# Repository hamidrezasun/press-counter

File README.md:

# Hydraulic press counter (v6.2)

Counts the strokes of a hydraulic die press, identifies operator and die by NFC card, switches the press contactor through an
on-board relay, shows the counter on a small OLED and reports to an MQTT broker. The stroke signal is the 230 V AC on the press
**contactor coil**, read through an optocoupler.

v6 is the "simple and cheap for mass production" revision: **one board, one chip.** An ESP32-WROOM-32 module does the counting, the relay,
the NFC reader, the display, the temperature probe and WiFi / MQTT / web page. The STM32, the ESP8266, the second board, the ribbon cable,
the 2.4in display and the ribbon cable of v5 are gone. The free ESP32 pins drive four extra output relays (COM / NO / NC) and read two DC inputs
(12/24 V sense, AUX, both 0-30 V). The board runs from 230 V (on-board HLK-5M05) **or** from a 5 V adapter on its own screw terminal (v6.2).
Parts cost about 2.9 M Toman of parts per unit (v5: about 5.1 M), every line checked on a shop page (eca.ir, voltatech.ir, javanelec.com, robochip.ir); without the four output relays about 2.5 M.

```
            ┌──────────────────────────── one board, 202 x 104 mm ────────────────────────────┐
 230 V ────►│ fuse · HLK-5M05 5 V (or 5 V adapter) · LDO ESP32-WROOM-32 (WiFi)    OLED 0.96in  │
 contactor ►│ 230 VAC opto input (MB10S + PC817)       USB micro-B (CH340G)      RC522 NFC    │
 coil       │ relay 5 V (COM / NO / NC) ──► press contactor control circuit                    │
            │ DS18B20 probe terminal · 2 call buttons · buzzer · LEDs                           │
            │ 4 output relays (COM / NO / NC) · 12/24 V and AUX inputs (0-30 V)                   │
            └───────────────────────────────────────────────────────────────────────────────────┘
```

| Folder | What |
|--------|------|
| `hardware/` | KiCad 10 project (generated from `tools/design.py`), fabrication files, BOM with Iranian-store links - [hardware/README.md](hardware/README.md) |
| `firmware/press_counter/` | the ESP32 firmware (Arduino sketch) - [docs/FIRMWARE.md](docs/FIRMWARE.md) |
| `docs/` | [DESIGN_REVIEW.md](docs/DESIGN_REVIEW.md) block-by-block check with calculations and open points, [PRODUCTION.md](docs/PRODUCTION.md) what to send to the board house / assembler and how to test, [INSTALLATION.md](docs/INSTALLATION.md) enclosure, wiring, labels, safety limits, [LASER_DIY.md](docs/LASER_DIY.md) prototype with a laser + drill, [ORDER_ESYS.md](docs/ORDER_ESYS.md) ordering at esys.ir, [SOURCING.md](docs/SOURCING.md) which shops (eca.ir + voltatech.ir cover everything), [FIRMWARE.md](docs/FIRMWARE.md), [PROTOCOL.md](docs/PROTOCOL.md) (MQTT topics, HTTP API), [REVIEW.md](docs/REVIEW.md) history of the design decisions |
| `hardware/archive_v5/`, `firmware/archive_v5/` | the previous two-board STM32 + ESP8266 design (reference only) |
| `V2/` | the old single-ESP8266 firmware for the v2 board (kept) |
| `analyzer/` | FastAPI + React dashboard that turns InfluxDB events into work sessions (needs an MQTT -> InfluxDB bridge such as Telegraf) |

## What it does

* **Strokes:** one MQTT event per stroke: `count`, `duration` (ms the contactor was energised), `temperature`; the lifetime counter survives power loss.
* **Who / what:** `personnel:<id>` card = start / end of a work session, switches the relay (enables the press); `die:<id>` card = which die is mounted.
* **Machine relay:** COM / NO / NC on a terminal; with COM-NO in the contactor control circuit the press is *disabled* whenever the board is unpowered, reset or hung (watchdog). Idle timeout and over-temperature switch it off. Remote start over the network is refused unless it was enabled in the settings; stop always works.
* **Local:** OLED with the counter, machine state, operator, temperature, errors (`Exx`), calls and the IP address; two call buttons (supervisor, net / maintenance), buzzer, red alarm LED, green "machine on" LED. Works without any network.
* **Extra I/O:** four output relays OUT1-OUT4 (COM / NO / NC, MQTT `relay/2..5/set`, or automatic: follow the machine, an alarm, a call, the press signal); 12/24 V sense input and AUX input, both 0-30 V (MQTT `sensor/voltage`).
* **Network:** WiFi with a setup access point, NTP, **MQTT** (status, events, `relay/1/set`, `cmd`), web page with every function and setting, ArduinoOTA and updates from your own server.
* **Power:** 230 VAC on J1, or a regulated 5 V adapter on J6 (protected: resettable fuse, TVS, reverse-polarity diode). No relay clicks while the board starts, resets or is programmed.
* **Programming:** one micro-USB cable, Arduino IDE (*ESP32 Dev Module*): the board's CH340G resets the ESP32 into its bootloader by itself, like an Arduino.

## Where it stands (honest status)

| Part | State |
|------|-------|
| PCB | 202 x 104 mm, 124 parts. ERC 0, DRC 0 violations / 0 unconnected / schematic parity OK (KiCad 10); the 5 mm mains creepage rule was shown to trigger on a deliberately wrong placement. **Never fabricated or powered.** Several footprints of generic parts must be checked against the real parts first - [docs/DESIGN_REVIEW.md](docs/DESIGN_REVIEW.md) section 8 |
| Firmware | **compiles** for the ESP32 (Arduino core esp32 3.3.12, no warnings with all warnings on): 1,248,699 bytes of the 1.9 MB app partition, 68.6 KB static RAM. **Never run on a chip** |
| Web page | checked in a browser against a mock (`firmware/tools/mock_device.py`) |
| Mains parts | 5 mm creepage enforced between mains and low voltage, 1 A time-lag fuse on the board; the relay coil / contact insulation is *basic* only - **a qualified person must do the mains wiring and first power-up** |

## Quick start

1. Read [docs/PRODUCTION.md](docs/PRODUCTION.md). Build 3-5 pilot boards first; order the PCB from `hardware/fabrication/main/press_counter_gerbers.zip` and the parts from `hardware/BOM_press_counter_v6.xlsx` (check the footprints of the real parts, see DESIGN_REVIEW).
2. Flash the firmware over USB from the Arduino IDE - [docs/FIRMWARE.md](docs/FIRMWARE.md).
3. Join the setup WiFi `PressCounter-XXXXXX` (password `presscounter`), enter your WiFi, then open the device's page (its IP is on the display): set the MQTT broker, an **admin password** and the OTA password.
4. Wire the contactor coil to `PRESS SENSE 230VAC` (J2), the press-contactor control circuit to the relay contact (J5, COM / NO), the DS18B20 probe to J4, mains to J1 (the 1 A fuse F1 is on the board). Never run the board with the enclosure open.

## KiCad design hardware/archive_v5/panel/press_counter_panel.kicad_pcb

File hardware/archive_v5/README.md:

# Archive: press counter v5 (two boards, STM32F103 + ESP8266)

Kept for reference only - superseded by the single-board ESP32 design v6 (see ../README.md).

* `fabrication/` - the last complete, DRC-clean v5.2 exports (MAIN 188 x 104 mm with five relays, PANEL 150 x 96 mm).
* `main/`, `panel/` - KiCad projects as they were when v6 was started (MAIN contains the unfinished v5.3 USB-programming changes).
* `tools/` - the v5 generator scripts (design.py, layout_main.py, layout_panel.py ...); they expect to live in `hardware/tools/`.
* `BOM_press_counter_v5.xlsx` - BOM of v5.3 (about 5.1 M Toman).

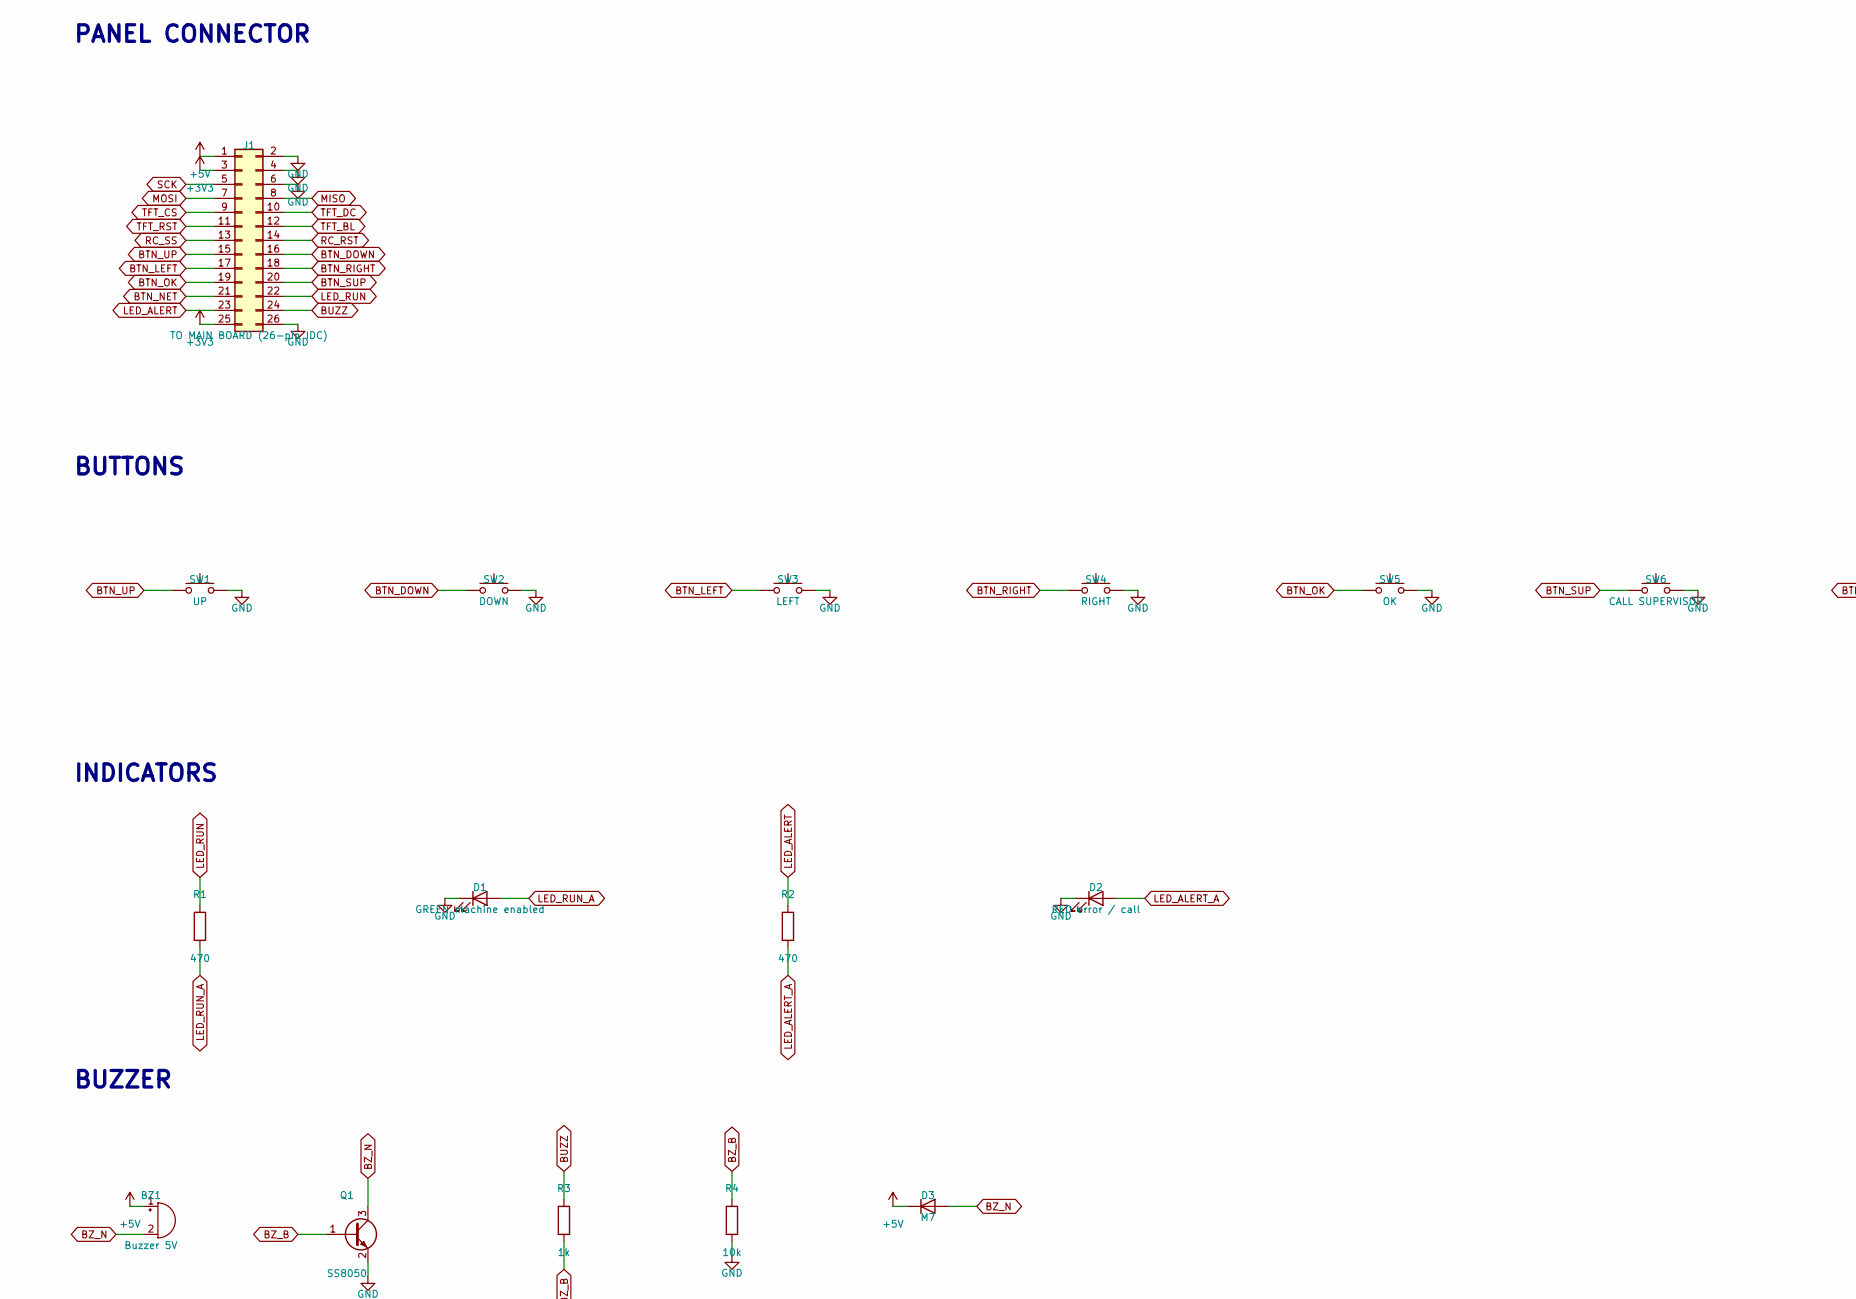
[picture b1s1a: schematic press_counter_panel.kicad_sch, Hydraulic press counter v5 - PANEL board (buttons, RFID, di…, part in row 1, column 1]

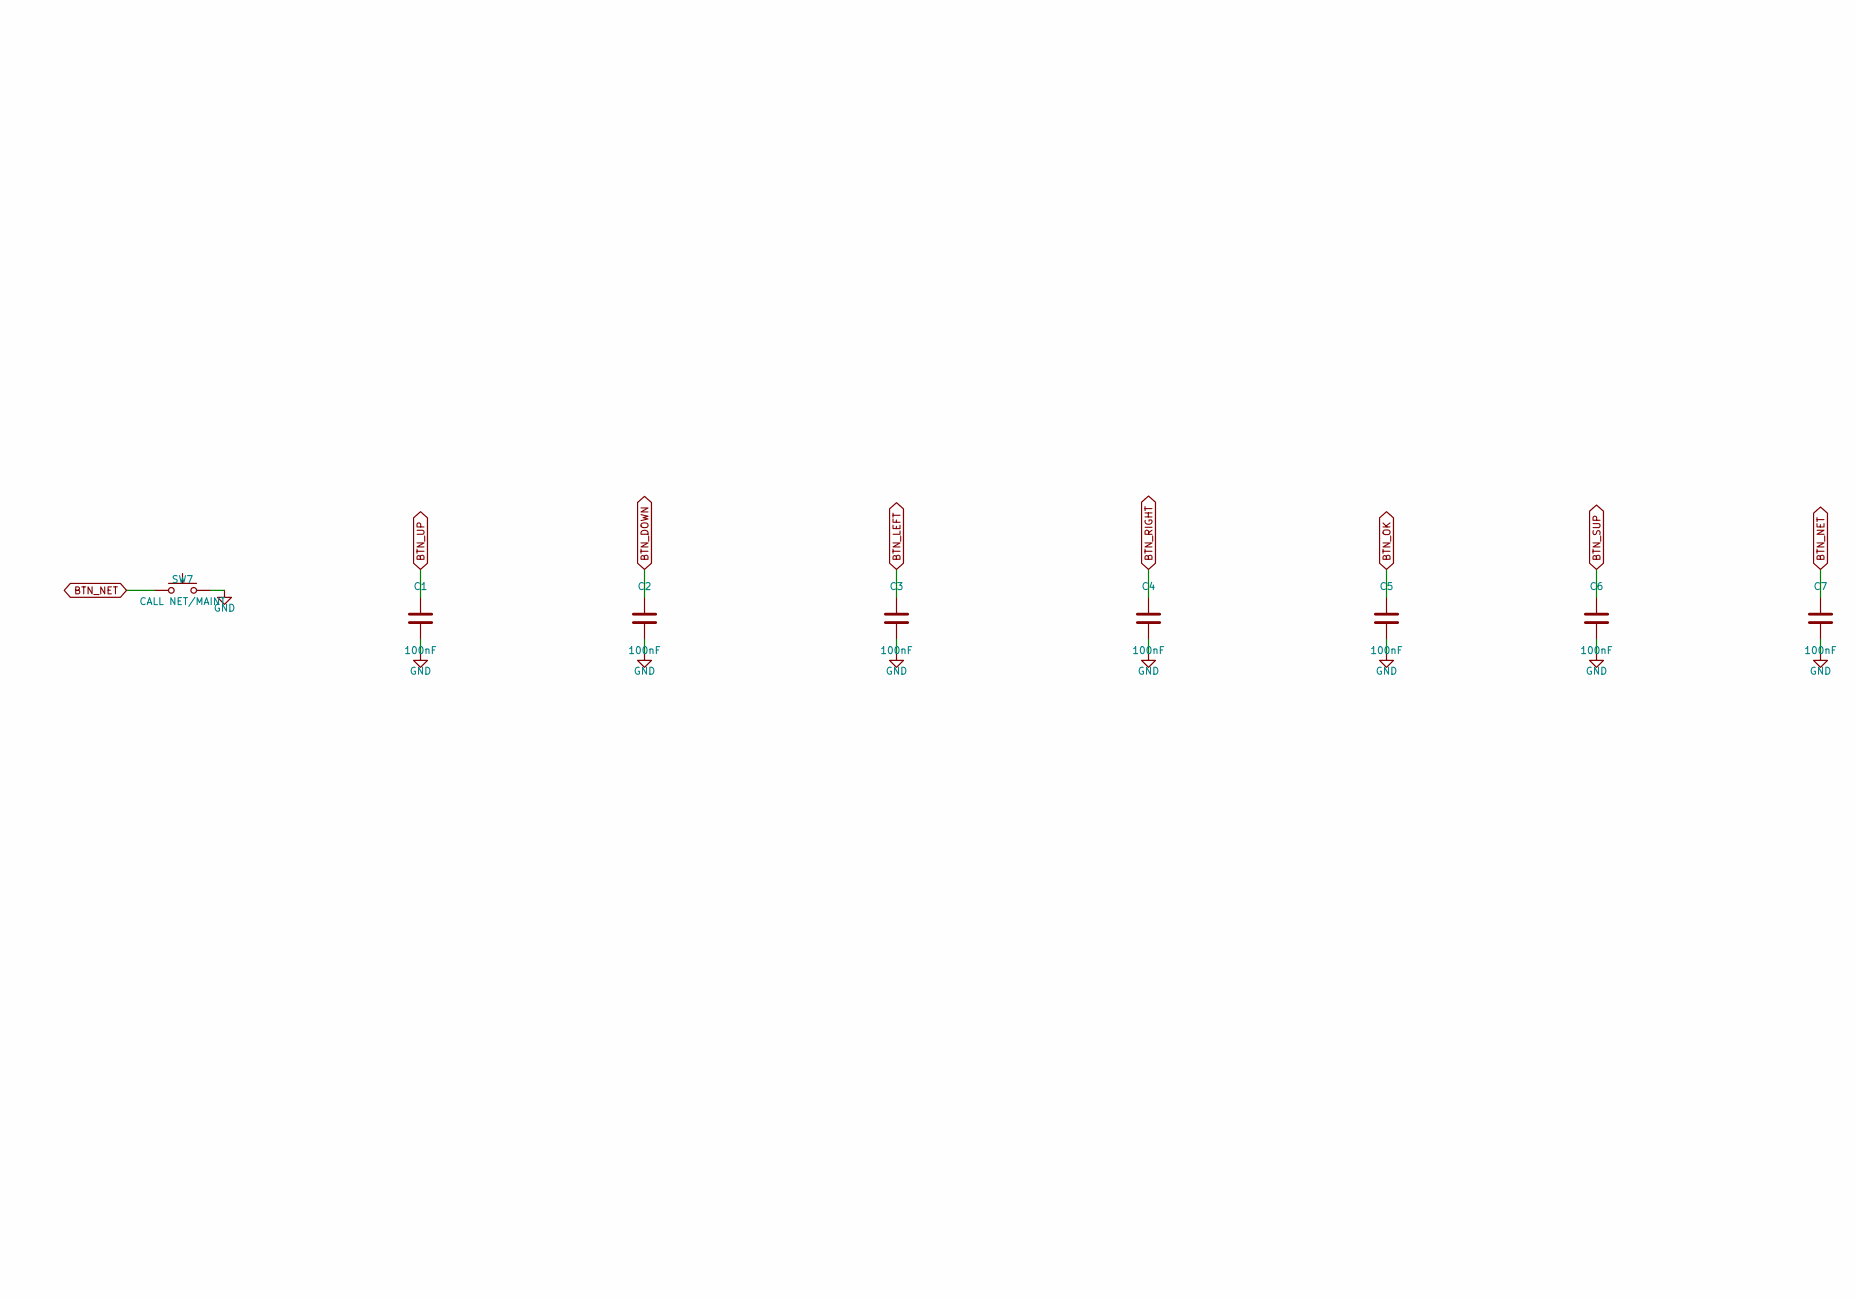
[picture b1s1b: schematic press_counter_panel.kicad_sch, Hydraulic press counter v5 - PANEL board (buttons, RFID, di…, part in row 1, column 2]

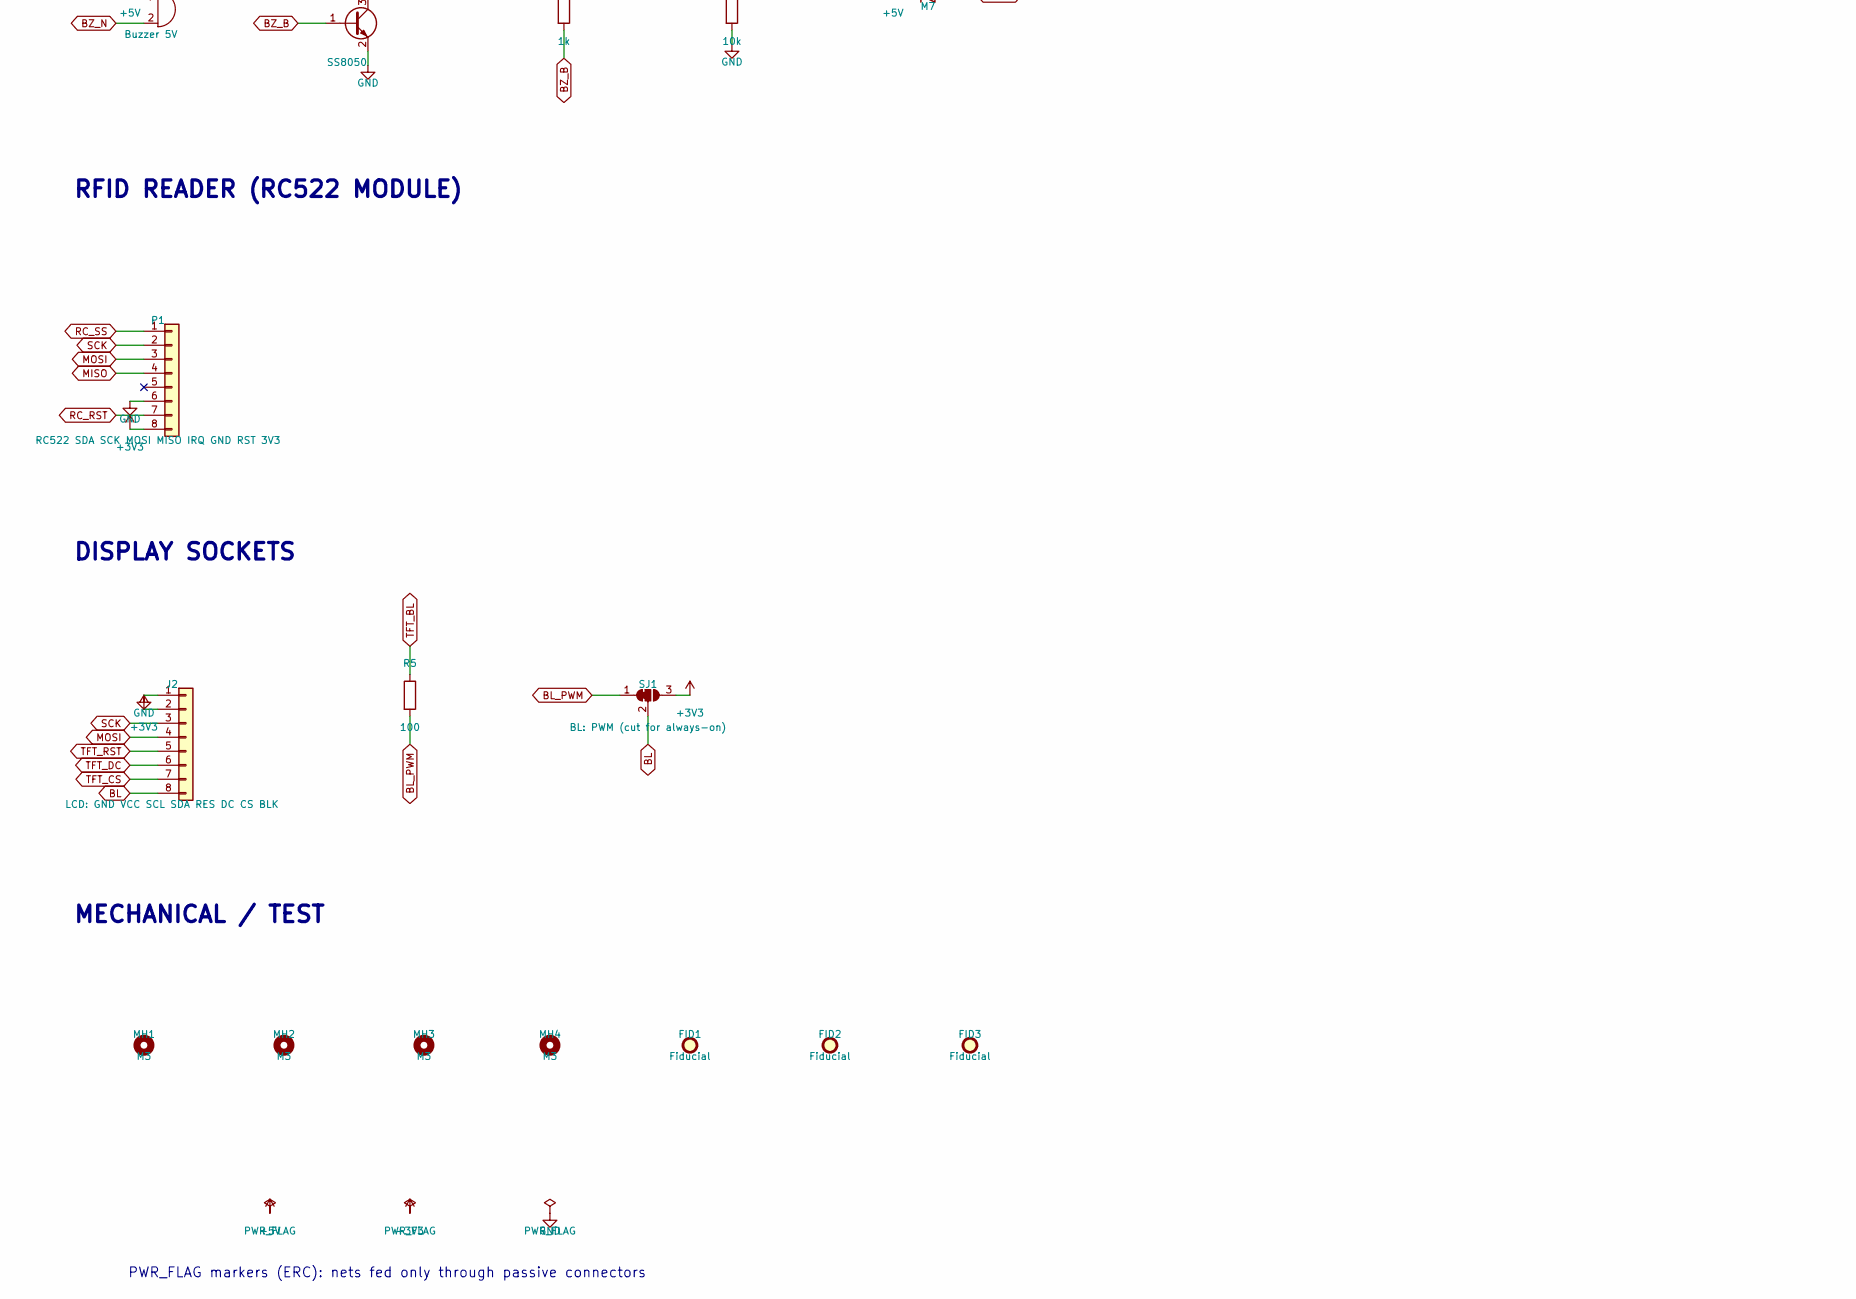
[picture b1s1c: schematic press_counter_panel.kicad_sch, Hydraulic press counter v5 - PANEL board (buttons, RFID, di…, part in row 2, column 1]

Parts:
BZ1: Buzzer 5V; Buzzer_12x9.5RM7.6
C1, C2, C3, C4, C5, C6, C7: 100nF; C_1206_3216Metric
D1: GREEN machine enabled; LED_0805_2012Metric
D2: RED error / call; LED_0805_2012Metric
D3: M7; D_SMA
FID1, FID2, FID3: Fiducial; Fiducial_1mm_Mask2mm
J1: TO MAIN BOARD (26-pin IDC); IDC-Header_2x13_P2.54mm_Vertical
J2: LCD: GND VCC SCL SDA RES DC CS BLK; PinSocket_1x08_P2.54mm_Vertical
MH1, MH2, MH3, MH4: M3; MountingHole_3.2mm_M3
P1: RC522 SDA SCK MOSI MISO IRQ GND RST 3V3; PinSocket_1x08_P2.54mm_Vertical
Q1: SS8050; SOT-23
R1, R2: 470; R_0805_2012Metric
R3: 1k; R_0805_2012Metric
R4: 10k; R_0805_2012Metric
R5: 100; R_0805_2012Metric
SJ1: BL: PWM (cut for always-on); SolderJumper-3_P1.3mm_Bridged12_Pad1.0x1.5mm
SW1: UP; SW_SPST_B3S-1000
SW2: DOWN; SW_SPST_B3S-1000
SW3: LEFT; SW_SPST_B3S-1000
SW4: RIGHT; SW_SPST_B3S-1000
SW5: OK; SW_SPST_B3S-1000
SW6: CALL SUPERVISOR; SW_SPST_B3S-1000
SW7: CALL NET/MAINT; SW_SPST_B3S-1000

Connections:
+3V3: J1.3, J1.25, J2.2, P1.8, SJ1.3 (B)
+5V: BZ1.1 (+), D3.1 (K), J1.1
BL: J2.8, SJ1.2 (C)
BL_PWM: R5.2, SJ1.1 (A)
BTN_DOWN: C2.1, J1.16, SW2.1
BTN_LEFT: C3.1, J1.17, SW3.1
BTN_NET: C7.1, J1.21, SW7.1
BTN_OK: C5.1, J1.19, SW5.1
BTN_RIGHT: C4.1, J1.18, SW4.1
BTN_SUP: C6.1, J1.20, SW6.1
BTN_UP: C1.1, J1.15, SW1.1
BUZZ: J1.24, R3.1
BZ_B: Q1.1 (B), R3.2, R4.1
BZ_N: BZ1.2 (-), D3.2 (A), Q1.3 (C)
GND: C1.2, C2.2, C3.2, C4.2, C5.2, C6.2, C7.2, D1.1 (K), D2.1 (K), J1.2, J1.4, J1.6, J1.26, J2.1, P1.6, Q1.2 (E), R4.2, SW1.2, SW2.2, SW3.2, SW4.2, SW5.2, SW6.2, SW7.2
LED_ALERT: J1.23, R2.1
LED_ALERT_A: D2.2 (A), R2.2
LED_RUN: J1.22, R1.1
LED_RUN_A: D1.2 (A), R1.2
MISO: J1.8, P1.4
MOSI: J1.7, J2.4, P1.3
RC_RST: J1.14, P1.7
RC_SS: J1.13, P1.1
SCK: J1.5, J2.3, P1.2
TFT_BL: J1.12, R5.1
TFT_CS: J1.9, J2.7
TFT_DC: J1.10, J2.6
TFT_RST: J1.11, J2.5

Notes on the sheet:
PANEL CONNECTOR
BUTTONS
INDICATORS
BUZZER
RFID READER (RC522 MODULE)
DISPLAY SOCKETS
MECHANICAL / TEST
PWR_FLAG markers (ERC): nets fed only through passive connectors

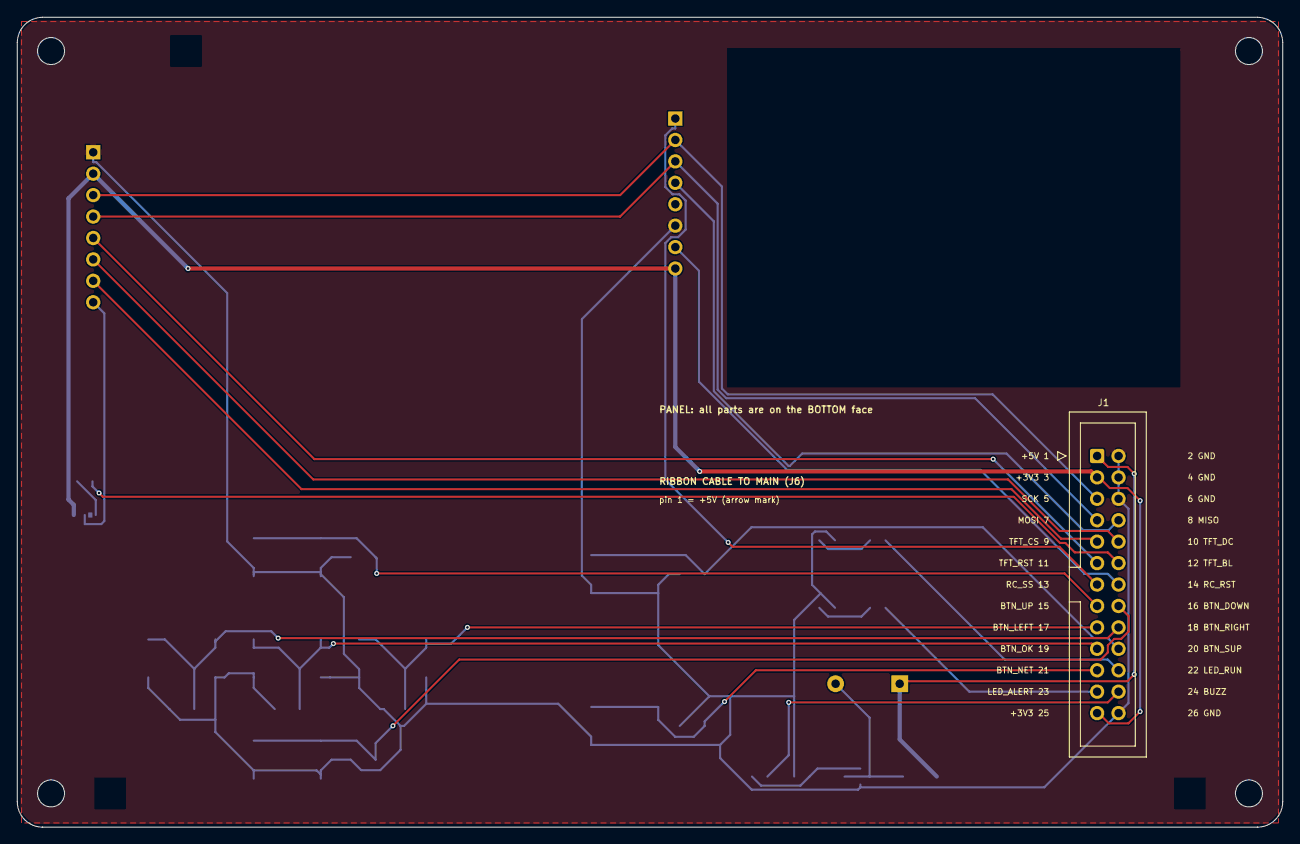
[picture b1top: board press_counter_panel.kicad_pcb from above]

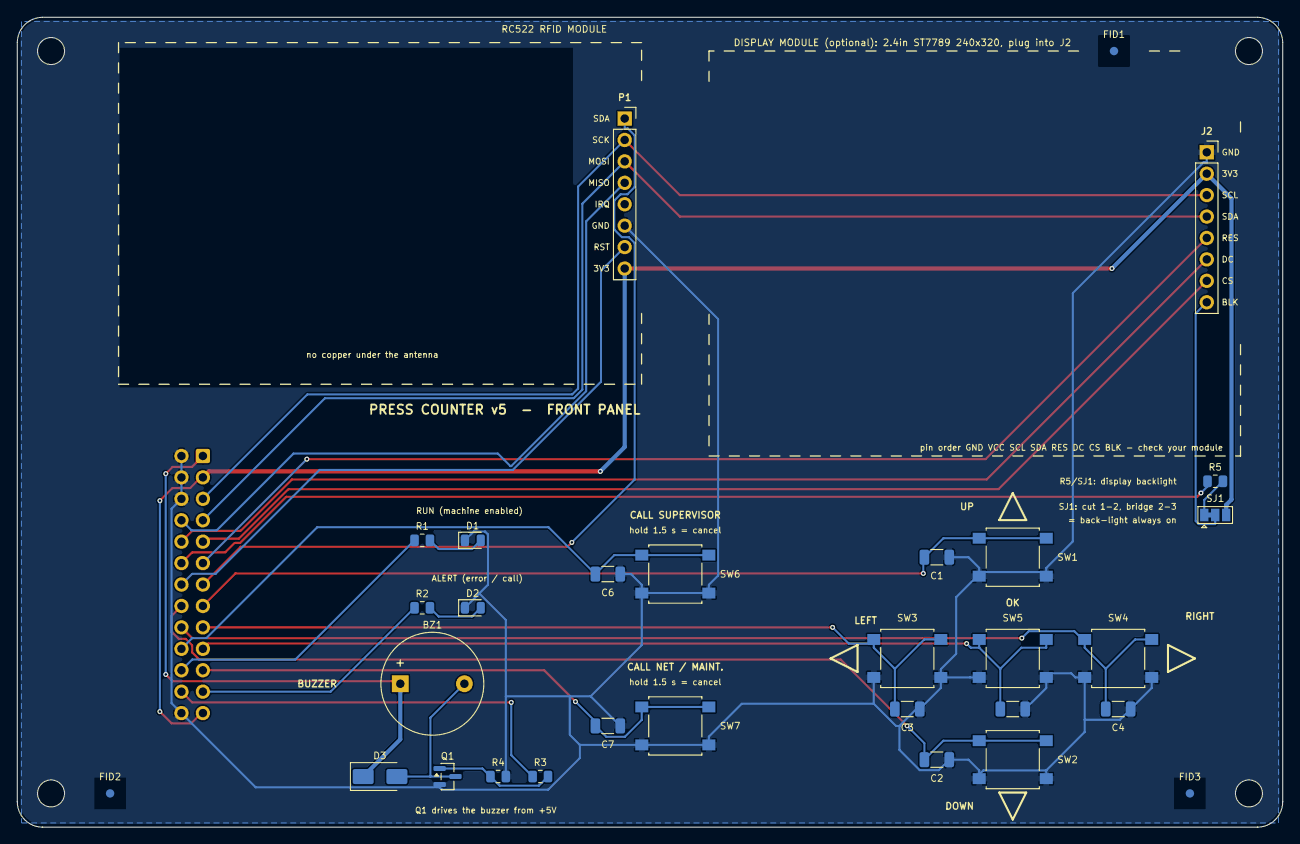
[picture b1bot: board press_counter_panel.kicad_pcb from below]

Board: 2 copper layers, 150.0 x 96.0 mm, 35 parts (30 on the bottom side), 28 nets.

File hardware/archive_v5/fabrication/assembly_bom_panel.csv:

Designator,Value,Footprint,Description,Mounting + side,DNP,Group
J1,TO MAIN BOARD (26-pin IDC),IDC-Header_2x13_P2.54mm_Vertical,IDC box header 2x13 + 26-wire ribbon cable,THT top,,PANEL CONNECTOR
SW1,UP,SW_SPST_B3S-1000,Tactile switch 6x6x5 SMD,SMD bottom,,BUTTONS
SW2,DOWN,SW_SPST_B3S-1000,Tactile switch 6x6x5 SMD,SMD bottom,,BUTTONS
SW3,LEFT,SW_SPST_B3S-1000,Tactile switch 6x6x5 SMD,SMD bottom,,BUTTONS
SW4,RIGHT,SW_SPST_B3S-1000,Tactile switch 6x6x5 SMD,SMD bottom,,BUTTONS
SW5,OK,SW_SPST_B3S-1000,Tactile switch 6x6x5 SMD,SMD bottom,,BUTTONS
SW6,CALL SUPERVISOR,SW_SPST_B3S-1000,Tactile switch 6x6x5 SMD,SMD bottom,,BUTTONS
SW7,CALL NET/MAINT,SW_SPST_B3S-1000,Tactile switch 6x6x5 SMD,SMD bottom,,BUTTONS
C1,100nF,C_1206_3216Metric,100nF 50V X7R 1206,SMD bottom,,BUTTONS
C2,100nF,C_1206_3216Metric,100nF 50V X7R 1206,SMD bottom,,BUTTONS
C3,100nF,C_1206_3216Metric,100nF 50V X7R 1206,SMD bottom,,BUTTONS
C4,100nF,C_1206_3216Metric,100nF 50V X7R 1206,SMD bottom,,BUTTONS
C5,100nF,C_1206_3216Metric,100nF 50V X7R 1206,SMD bottom,,BUTTONS
C6,100nF,C_1206_3216Metric,100nF 50V X7R 1206,SMD bottom,,BUTTONS
C7,100nF,C_1206_3216Metric,100nF 50V X7R 1206,SMD bottom,,BUTTONS
R1,470,R_0805_2012Metric,470R 0805,SMD bottom,,INDICATORS
D1,GREEN machine enabled,LED_0805_2012Metric,LED 0805 green,SMD bottom,,INDICATORS
R2,470,R_0805_2012Metric,470R 0805,SMD bottom,,INDICATORS
D2,RED error / call,LED_0805_2012Metric,LED 0805 red,SMD bottom,,INDICATORS
BZ1,Buzzer 5V,Buzzer_12x9.5RM7.6,Buzzer 12mm 5V (active),THT bottom,,BUZZER
Q1,SS8050,SOT-23,SS8050 SOT-23,SMD bottom,,BUZZER
R3,1k,R_0805_2012Metric,1k 0805,SMD bottom,,BUZZER
R4,10k,R_0805_2012Metric,10k 0805,SMD bottom,,BUZZER
D3,M7,D_SMA,1N4007 SMD (M7),SMD bottom,,BUZZER
P1,RC522 SDA SCK MOSI MISO IRQ GND RST 3V3,PinSocket_1x08_P2.54mm_Vertical,Female header 1x8 (for the RC522 module),THT bottom,,RFID READER (RC522 MODULE)
J2,LCD: GND VCC SCL SDA RES DC CS BLK,PinSocket_1x08_P2.54mm_Vertical,Female header 1x8 (2.4in ST7789 display module),THT bottom,optional (display),DISPLAY SOCKETS
R5,100,R_0805_2012Metric,100R 0805,SMD bottom,optional (display),DISPLAY SOCKETS

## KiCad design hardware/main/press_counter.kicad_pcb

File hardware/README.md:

# Press counter v6.2 - hardware (KiCad 10)

One 2-layer board, generated from one file, [`tools/design.py`](tools/design.py) (parts + nets), so schematic, PCB and BOM cannot disagree.
Review with calculations and open points: [../docs/DESIGN_REVIEW.md](../docs/DESIGN_REVIEW.md). Production / test: [../docs/PRODUCTION.md](../docs/PRODUCTION.md).

| Board | Size | What |
|-------|------|------|
| `main/press_counter.*` | 202 x 104 mm, 124 parts | mains input + T1A fuse + HLK-5M05, 230 VAC press-sense optocoupler, 5 V relay (COM / NO / NC), **ESP32-WROOM-32**, USB micro-B with CH340G auto-reset, sockets for the **RC522** NFC module and the **0.96in I2C OLED**, DS18B20 terminal, 2 call buttons, buzzer, LEDs; **4 output relays** (COM / NO / NC) in a strip on the right edge; **12/24 V and AUX inputs (0-30 V)**; **5 V screw terminal** as an alternative to the mains supply |

```
hardware/
  main/                    KiCad project (open press_counter.kicad_pro), drc.rpt, erc.rpt
  fabrication/main/        press_counter_gerbers.zip, gerbers/ (RS-274X + Excellon PTH / NPTH), positions.csv, pcb_layers.pdf, schematic.pdf, render_top|bottom.png
  fabrication/assembly_bom.csv   designators / values / footprints / SMD-THT
  lib/press_counter.pretty custom footprints (wide SOP-4 for the PC817, 5x20 PCB fuse holder with slotted holes, ESP32 with 0.3 mm GND vias)
  BOM_press_counter_v6.xlsx   Iranian-store links + prices (2026-10-12), sheet "Production" scales to N units
  fabrication/check/       print_1to1_A4_top.pdf: print at 100 % and lay the real parts on it (footprint check before ordering boards)
  fabrication/esys/        press_counter_esys_gerber.zip: Gerber + drill files named for esys.ir (make_esys_package.py, check_esys.py) - see docs/ORDER_ESYS.md
  fabrication/laser/       laser-etch bitmaps (top / mirrored bottom), drill list, test pattern (make_laser_files.py) - see docs/LASER_DIY.md
  fabrication/enclosure/   enclosure_interface.svg / .csv: openings, light pipes, cable entries (make_enclosure_drawing.py)
  tools/                   generators - see "Regenerating"
  sim/                     SPICE checks run with KiCad's ngspice: sense_input.py (230 V input), relay_driver.py (relay at start-up)
  archive_v5/              the previous two-board design (MAIN + PANEL, STM32 + ESP8266) with its fabrication files
```

**Help on the board:** the front silk names the pins of every connector and socket; the **back carries a help sheet** (terminals, wire colours,
LEDs, test points). Fiducials FID1-3, test points TP1 (+5 V), TP2 (+3.3 V), TP3 (GND), TP4 (PRESS).

## Blocks

| Block | Parts | Notes |
|-------|-------|-------|
| Mains in | J1 (L, N), **F1 fuse holder 5x20 + T1A 250 V**, RV1 varistor, PS1 Hi-Link HLK-5M05, C1 / C2 | 230 V -> 5 V / 1 A isolated module. Fuse in L, before the varistor. |
| 5 V terminal (v6.2) | **J6 (+5V, GND)** at the top edge, F2 PTC 1.1 A / 60 V, D7 SMBJ6.5A, D8 SS34 | instead of mains: a regulated 5 V / >= 1.5 A adapter. Reverse polarity / wrong adapter (up to 60 V): D7 conducts, F2 trips. D8 blocks back-feeding (mains and adapter together do no harm). |
| Press-sense input | J2 (SNS A/B), RV2, **RS1 120 k 1 W axial**, **BR1 MB10S**, C5 22 uF, D5 (red), U2 PC817, R12 2.2 k (threshold), R1 22 k | 230 V AC across the contactor coil -> 120 k -> bridge -> LED + optocoupler -> IO34 LOW while the contactor is energised. |
| Relay | K1 T73 / SRD-05VDC-SL-C **5 V coil** (SPDT, 10 A 250 V), Q2 SS8050, R9 / R13, D12 M7, D13 (green "ON") + R43, **J5 (NO, COM, NC)** | COM-NO in series with the contactor control circuit: **the press is disabled whenever the board is unpowered, booting or reset.** Contact tracks ~2.5 A. |
| 3.3 V | U3 AMS1117-3.3, C3, C4, D6 (green PWR) + R2 | 3V3 copper around the tab as a heat sink |
| Controller | U1 **ESP32-WROOM-32** (antenna at the top edge, copper-free 48 x 7 mm), C16 / C17, EN RC R51 / C18, IO0 pull-up R53 | one chip for counting, relay, NFC, display, temperature, WiFi / MQTT / web page |
| USB | J3 micro-B, D14 SS34 (VBUS -> +5 V), **U5 CH340G** + Y2 12 MHz + C25 / C26, R97, C22, Q7 / Q8 + R94 / R95 (DTR / RTS auto-reset) | upload from the Arduino IDE without buttons + 115200 console; USB powers the logic for bench work |
| NFC | P1 1x8 socket for the **RC522 module** (`SDA SCK MOSI MISO IRQ GND RST 3V3`), R33 | the module lies over the board; no copper under its antenna coil |
| Display | P2 1x4 socket for the **0.96in OLED** (`GND VCC SCL SDA`), R40 / R41 2.2 k | check the module's pin order |
| Temperature | J4 (3V3, DATA, GND), R10 2.2 k pull-up, R11 100 R | **DS18B20 waterproof probe** |
| Output relays | K2-K5 (OUT1-OUT4, T73 5 V), Q3-Q6 SS8050, R60-R63 1 k, R70-R73 10 k, D20-D23 M7, D30-D33 yellow + R80-R83, **J10-J13 (NO, COM, NC)** | IO27 / IO16 / IO25 / IO13; strip on the right edge (x > 150 mm), wire entry at the edge. Contacts 230 V, about 2.5 A. |
| Voltage inputs | J7 12/24 V sense (R90 100 k / R91 10 k, C20 -> IO36), J9 AUX (R98 100 k / R99 10 k, C23 -> IO35), both 0-30 V (36 V max.) | ADC1 pins (usable with WiFi). IO39 is free (the ZMPT101B header of v6.1 was removed). |
| Front | SW1 CALL SUPERVISOR, SW2 CALL NET (+ R20 / R21, C7 / C8), D2 red ALARM + R44 (IO15), BZ1 active buzzer (IO14) + Q1 / R3 / R4 / D3 | |

ESP32 pin map: [../docs/FIRMWARE.md](../docs/FIRMWARE.md) "Pins".

## Mains safety rules (enforced in the design files)

* Mains copper exists only in the left part of the board: supply input (J1, F1, RV1, PS1 AC pins), the press-sense input (J2 ... PC817 pins 1-2)
  the relay contacts (K1, J5) in the bottom-left corner and the output relay contacts (K2-K5, J10-J13) in the right strip. Dashed outlines on the silk.
* **5 mm clearance between mains copper and any low-voltage copper** (reinforced insulation, 250 V, pollution degree 2), enforced by the router and
  by DRC rules in `press_counter.kicad_dru`. Pad pairs inside a certified part (HLK module, PC817, relay) are exempt. **The relay's coil-to-contact
  insulation is basic only**: the front (buttons, OLED, NFC, USB) must be behind a closed insulating enclosure.
* 1.5 mm between different mains nets; 1.5 mm from mains copper to the board edge.
* Fuse: **T1A, 5x20 mm, slow-blow, in the on-board holder F1.** Mains wiring and the first power-up are for a qualified person.
* J2 goes across the contactor **coil** (220-240 V AC). LED current = (V x 0.9 - 4.5 V) / 120 k. Sense timing: C5 bridges the zero crossings, so the
  release is seen ~20-40 ms late; set *Minimum stroke signal* to 20-30 ms.

## Verification status (KiCad 10.0.6, 2026-10-11)

| Check | Result |
|-------|--------|
| ERC | 0 errors, 0 warnings; netlist check against design.py: 0 differences |
| DRC incl. schematic parity, all track errors, silk | **0 violations, 0 unconnected, 0 footprint errors** |
| Creepage rule 5 mm mains <-> low voltage | active - negative test: a low-voltage resistor 3 mm beside a mains track gave four `mains_ac_to_lv` errors, the real board none |
| Routing | 1007 tracks, 116 vias (0.6 / 0.3 mm), smallest hole 0.3 mm, no vias on the mains nets |

How it was routed: the mains nets by an own grid router (class clearances, 5 mm creepage, hand-placed relay-coil stubs), the rest by Freerouting 2.5.0
(headless, Java 25), then a small island-repair step for the nets the autorouter left incomplete.

**Not verified** (needs a person / the physical parts / a bench): electrical function of anything, the footprints of the micro-USB connector, PC817 SMD,
buzzer, tact switch, fuse holder, relay and terminal blocks against the exact parts you receive, WiFi range in the enclosure, NFC read distance,
thermal behaviour, EMC / ESD. The board has never been fabricated.

## Regenerating (KiCad's own Python, Java for Freerouting)

`tools\run_all.bat` runs everything (schematic + ERC, place + route, island repair, DRC, silk, fabrication files). Individual steps (run with
`D:\KiCad\10.0\bin\python.exe -P`):

| Command | What |
|---------|------|
| `gen_all.py main` | schematic + ERC + netlist check |
| `route_fr.py main [--passes N] [--reuse-ses]` | placement, mains routing, Freerouting (`--reuse-ses` re-imports the last result) |
| `repair.py main <net> --apply --inplace` | join the islands of a net the autorouter left incomplete |
| `finish.py main [--no-export]` | zone fill, DRC, gerbers / drill / zip / position / PDF / renders |
| `cleanup.py main`, `resilk.py main` | remove dangling copper reported by the DRC / rebuild the silkscreen without re-routing |
| `make_custom_lib.py` (any Python) | the custom footprints in `lib/press_counter.pretty` |
| `make_bom.py` (system Python + openpyxl) | `BOM_press_counter_v6.xlsx` + `fabrication/assembly_bom.csv` |
| `placecheck.py main` | courtyard / silk overlap check of the placement only |

Freerouting 2.5.0 needs `tools/freerouting/freerouting-2.5.0.jar` and a Java 25 runtime in `tools/freerouting/jre25/` (downloaded, not committed);
without them `route_fr.py` falls back to the 1.9.0 jar. Edit `design.py` / `layout_main.py`, not the generated KiCad files.

Gotchas learned: KiCad **silently ignores the whole `.kicad_dru`** if one rule has an unknown property; `pcbnew`'s `Save()` rewrites the `.kicad_pro`
(losing net classes) - `project.py` re-writes both after every save; after `BOARD.Remove()` the SWIG getters return untyped objects; pin names with
`/` become `{slash}` in KiCad's unconnected-net names.

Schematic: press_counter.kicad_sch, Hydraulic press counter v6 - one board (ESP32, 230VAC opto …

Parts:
BR1: MB10S; TO-269AA
BZ1: Buzzer 5V; Buzzer_12x9.5RM7.6
C1: 100uF 16V; CP_Elec_6.3x5.4
C2, C7, C8, C17, C20, C22, C23: 100nF; C_1206_3216Metric
C3, C16: 10uF; C_1206_3216Metric
C4: 47uF 16V; CP_Elec_6.3x5.4
C5: 22uF 35V; CP_Elec_5x5.4
C18: 1uF; C_1206_3216Metric
C25, C26: 22pF; C_0805_2012Metric
D2: RED error / call; LED_0805_2012Metric
D3, D12, D20, D21, D22, D23: M7; D_SMA
D5: RED mains present; LED_0805_2012Metric
D6: GREEN power; LED_0805_2012Metric
D7: SMBJ6.5A; D_SMB
D8, D14: SS34; D_SMA
D13: GREEN machine on; LED_0805_2012Metric
D30: YELLOW OUT1 on; LED_0805_2012Metric
D31: YELLOW OUT2 on; LED_0805_2012Metric
D32: YELLOW OUT3 on; LED_0805_2012Metric
D33: YELLOW OUT4 on; LED_0805_2012Metric
F1: 1A 250V T; FuseHolder_5x20_PCB_P22.5
F2: 1.1A 60V; C_Disc_D7.5mm_W5.0mm_P5.00mm
FID1, FID2, FID3: Fiducial; Fiducial_1mm_Mask2mm
J1: MAINS 230VAC; TerminalBlock_Phoenix_MKDS-1,5-2-5.08_1x02_P5.08mm_Horizont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
J2: PRESS SENSE 230VAC; TerminalBlock_Phoenix_MKDS-1,5-2-5.08_1x02_P5.08mm_Horizont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
J3: USB micro-B; USB_Micro-B_Wuerth_629105150521
J4: DS18B20: 3V3 DATA GND; TerminalBlock_Phoenix_MKDS-1,5-3-5.08_1x03_P5.08mm_Horizont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
J5: RELAY CONTACT: NO, COM, NC; TerminalBlock_Phoenix_MKDS-1,5-3-5.08_1x03_P5.08mm_Horizont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
J6: 5V DC IN: +5V, GND; TerminalBlock_Phoenix_MKDS-1,5-2-5.08_1x02_P5.08mm_Horizont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
J7: 12/24V SENSE IN: +, GND; TerminalBlock_Phoenix_MKDS-1,5-2-5.08_1x02_P5.08mm_Horizont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
J9: AUX IN 0-30V: IN, GND; TerminalBlock_Phoenix_MKDS-1,5-2-5.08_1x02_P5.08mm_Horizont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
J10: OUT1 CONTACT: NO, COM, NC; TerminalBlock_Phoenix_MKDS-1,5-3-5.08_1x03_P5.08mm_Horizont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
J11: OUT2 CONTACT: NO, COM, NC; TerminalBlock_Phoenix_MKDS-1,5-3-5.08_1x03_P5.08mm_Horizont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
J12: OUT3 CONTACT: NO, COM, NC; TerminalBlock_Phoenix_MKDS-1,5-3-5.08_1x03_P5.08mm_Horizont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
J13: OUT4 CONTACT: NO, COM, NC; TerminalBlock_Phoenix_MKDS-1,5-3-5.08_1x03_P5.08mm_Horizont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
K1, K2, K3, K4, K5: SRD-05VDC-SL-C; Relay_SPDT_SANYOU_SRD_Series_Form_C
MH1, MH2, MH3, MH4, MH5, MH6: M3; MountingHole_3.2mm_M3
P1: RC522 SDA SCK MOSI MISO IRQ GND RST 3V3; PinSocket_1x08_P2.54mm_Vertical
P2: OLED GND VCC SCL SDA; PinSocket_1x04_P2.54mm_Vertical
PS1: HLK-5M05; Converter_ACDC_Hi-Link_HLK-5Mxx
Q1, Q2, Q3, Q4, Q5, Q6, Q7, Q8: SS8050; SOT-23
R1: 22k; R_0805_2012Metric
R2, R3, R9, R43, R60, R61, R62, R63, R80, R81, R82, R83: 1k; R_0805_2012Metric
R4, R13, R20, R21, R33, R51, R53, R70, R71, R72, R73, R91, R94, R95, R99: 10k; R_0805_2012Metric
R10, R12, R40, R41: 2.2k; R_0805_2012Metric
R11: 100; R_0805_2012Metric
R44: 470; R_0805_2012Metric
R90, R98: 100k; R_0805_2012Metric
R97: 0; R_0805_2012Metric
RS1: 120k 1W; R_Axial_DIN0411_L9.9mm_D3.6mm_P15.24mm_Horizontal
RV1, RV2: 7D471K; RV_Disc_D7mm_W3.4mm_P5mm
SW1: CALL SUPERVISOR; SW_SPST_B3S-1000
SW2: CALL NET/MAINT; SW_SPST_B3S-1000
TP1: +5V; TestPoint_Pad_D1.5mm
TP2: +3V3; TestPoint_Pad_D1.5mm
TP3: GND; TestPoint_Pad_D1.5mm
TP4: PRESS; TestPoint_Pad_D1.5mm
U1: ESP32-WROOM-32; ESP32-WROOM-32_Via03
U2: PC817 SMD; SOP4_Wide_Universal
U3: AMS1117-3.3; SOT-223-3_TabPin2
U5: CH340G; SOIC-16_3.9x9.9mm_P1.27mm
Y2: 12MHz; Crystal_SMD_HC49-SD

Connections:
+3V3: C4.1, C16.1, C17.1, C22.1, J4.1, P1.8, P2.2, R1.2, R2.1, R10.2, R20.2, R21.2, R33.2, R40.2, R41.2, R51.2, R53.2, R97.2, TP2.1, U1.2 (VDD), U3.2 (VO), U5.16 (VCC)
+5V: BZ1.1 (+), C1.1, C2.1, C3.1, D3.1 (K), D8.1 (K), D12.1 (K), D14.1 (K), D20.1 (K), D21.1 (K), D22.1 (K), D23.1 (K), K1.2, K2.2, K3.2, K4.2, K5.2, PS1.4 (+Vout), R43.1, R80.1, R81.1, R82.1, R83.1, TP1.1, U3.3 (VI)
ALERT_A: D2.2 (A), R44.2
AUX_ADC: C23.1, R98.2, R99.1, U1.7 (IO35)
AUX_IN: J9.1, R98.1
BOOT: Q7.3 (C), R53.1, U1.25 (IO0)
BR_A: BR1.3, RS1.2
BR_N: BR1.2 (-), C5.2, R12.2, U2.2
BR_P: BR1.1 (+), C5.1, D5.2 (A)
BTN_NET: C8.1, R21.1, SW2.1, U1.9 (IO33)
BTN_SUP: C7.1, R20.1, SW1.1, U1.8 (IO32)
BUZZ: R3.1, U1.13 (IO14)
BZ_B: Q1.1 (B), R3.2, R4.1
BZ_N: BZ1.2 (-), D3.2 (A), Q1.3 (C)
CH_V3: R97.1, U5.4 (V3)
CH_XI: C25.1, U5.7 (XI), Y2.1
CH_XO: C26.1, U5.8 (XO), Y2.2
EN: C18.1, Q8.3 (C), R51.1, U1.3 (EN)
EXT5V: F2.1, J6.1
EXT5V_F: D7.1 (K), D8.2 (A), F2.2
GND: C1.2, C2.2, C3.2, C4.2, C7.2, C8.2, C16.2, C17.2, C18.2, C20.2, C22.2, C23.2, C25.2, C26.2, D2.1 (K), D6.1 (K), D7.2 (A), J3.5 (GND), J3.SH (Shield), J4.3, J6.2, J7.2, J9.2, P1.6, P2.1, PS1.3 (-Vout), Q1.2 (E), Q2.2 (E), Q3.2 (E), Q4.2 (E), Q5.2 (E), Q6.2 (E), R4.2, R13.2, R70.2, R71.2, R72.2, R73.2, R91.2, R99.2, SW1.2, SW2.2, TP3.1, U1.1 (GND), U1.15 (GND), U1.38 (GND), U1.39 (GND), U2.3, U3.1 (GND), U5.1 (GND)
L: F1.1, J1.1
LED_ALERT: R44.1, U1.23 (IO15)
LED_K: D5.1 (K), R12.1, U2.1
LF: F1.2, PS1.1 (AC/L), RV1.1
MISO: P1.4, U1.31 (IO19)
MOSI: P1.3, U1.37 (IO23)
N: J1.2, PS1.2 (AC/N), RV1.2
OUT1_B: Q3.1 (B), R60.2, R70.1
OUT1_COM: J10.2, K2.1
OUT1_CTRL: R60.1, U1.12 (IO27)
OUT1_LED_A: D30.2 (A), R80.2
OUT1_N: D20.2 (A), D30.1 (K), K2.5, Q3.3 (C)
OUT1_NC: J10.3, K2.4
OUT1_NO: J10.1, K2.3
OUT2_B: Q4.1 (B), R61.2, R71.1
OUT2_COM: J11.2, K3.1
OUT2_CTRL: R61.1, U1.27 (IO16)
OUT2_LED_A: D31.2 (A), R81.2
OUT2_N: D21.2 (A), D31.1 (K), K3.5, Q4.3 (C)
OUT2_NC: J11.3, K3.4
OUT2_NO: J11.1, K3.3
OUT3_B: Q5.1 (B), R62.2, R72.1
OUT3_COM: J12.2, K4.1
OUT3_CTRL: R62.1, U1.10 (IO25)
OUT3_LED_A: D32.2 (A), R82.2
OUT3_N: D22.2 (A), D32.1 (K), K4.5, Q5.3 (C)
OUT3_NC: J12.3, K4.4
OUT3_NO: J12.1, K4.3
OUT4_B: Q6.1 (B), R63.2, R73.1
OUT4_COM: J13.2, K5.1
OUT4_CTRL: R63.1, U1.16 (IO13)
OUT4_LED_A: D33.2 (A), R83.2
OUT4_N: D23.2 (A), D33.1 (K), K5.5, Q6.3 (C)
OUT4_NC: J13.3, K5.4
OUT4_NO: J13.1, K5.3
PRESS: R1.1, TP4.1, U1.6 (IO34), U2.4
PROG_QB0: Q7.1 (B), R94.2
PROG_QB1: Q8.1 (B), R95.2
PWR_LED_A: D6.2 (A), R2.2
RC_RST: P1.7, U1.28 (IO17)
RC_SS: P1.1, R33.1, U1.29 (IO5)
RELAY_CTRL: R9.1, U1.11 (IO26)
RLY_B: Q2.1 (B), R9.2, R13.1
RLY_COM: J5.2, K1.1
RLY_LED_A: D13.2 (A), R43.2
RLY_N: D12.2 (A), D13.1 (K), K1.5, Q2.3 (C)
RLY_NC: J5.3, K1.4
RLY_NO: J5.1, K1.3
RXD: U1.34 (RXD0/IO3), U5.2 (TXD)
SCK: P1.2, U1.30 (IO18)
SCL: P2.3, R40.1, U1.36 (IO22)
SDA: P2.4, R41.1, U1.33 (IO21)
SENSE_A: J2.1, RS1.1, RV2.1
SENSE_B: BR1.4, J2.2, RV2.2
TEMP_DQ: J4.2, R10.1, R11.1
TEMP_IO: R11.2, U1.26 (IO4)
TXD: U1.35 (TXD0/IO1), U5.3 (RXD)
UDM: J3.2 (D-), U5.6 (UD-)
UDP: J3.3 (D+), U5.5 (UD+)
USB_DTR: Q7.2 (E), R95.1, U5.13 (~DTR)
USB_RTS: Q8.2 (E), R94.1, U5.14 (~RTS)
V12_ADC: C20.1, R90.2, R91.1, U1.4 (SENSOR_VP)
V12_IN: J7.1, R90.1
VBUS: D14.2 (A), J3.1 (VBUS)

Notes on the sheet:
MAINS INPUT & 5V SUPPLY
ALTERNATIVE 5 V INPUT (5 V ADAPTER INSTEAD OF MAINS)
3.3V REGULATOR
PRESS CONTACTOR RELAY (CONNECT / DISCONNECT)
PRESS-SENSE INPUT (230VAC -> OPTOCOUPLER)
CONTROLLER (ESP32-WROOM-32: COUNTER + WIFI)
USB PROGRAMMING (CH340G, AUTO-RESET)
OUTPUT RELAYS OUT1-OUT4 (COM / NO / NC)
VOLTAGE INPUTS: 12/24 V SENSE, AUX (0-30 V)
CALL BUTTONS, ALERT LED, BUZZER
NFC READER (RC522 MODULE)
DISPLAY (0.96in I2C OLED MODULE)
TEMPERATURE PROBE (DS18B20)
MECHANICAL / TEST
PWR_FLAG markers (ERC): nets fed only through passive connectors
